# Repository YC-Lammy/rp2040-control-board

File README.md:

# rp2040-control-board
 a control board based on the rp2040

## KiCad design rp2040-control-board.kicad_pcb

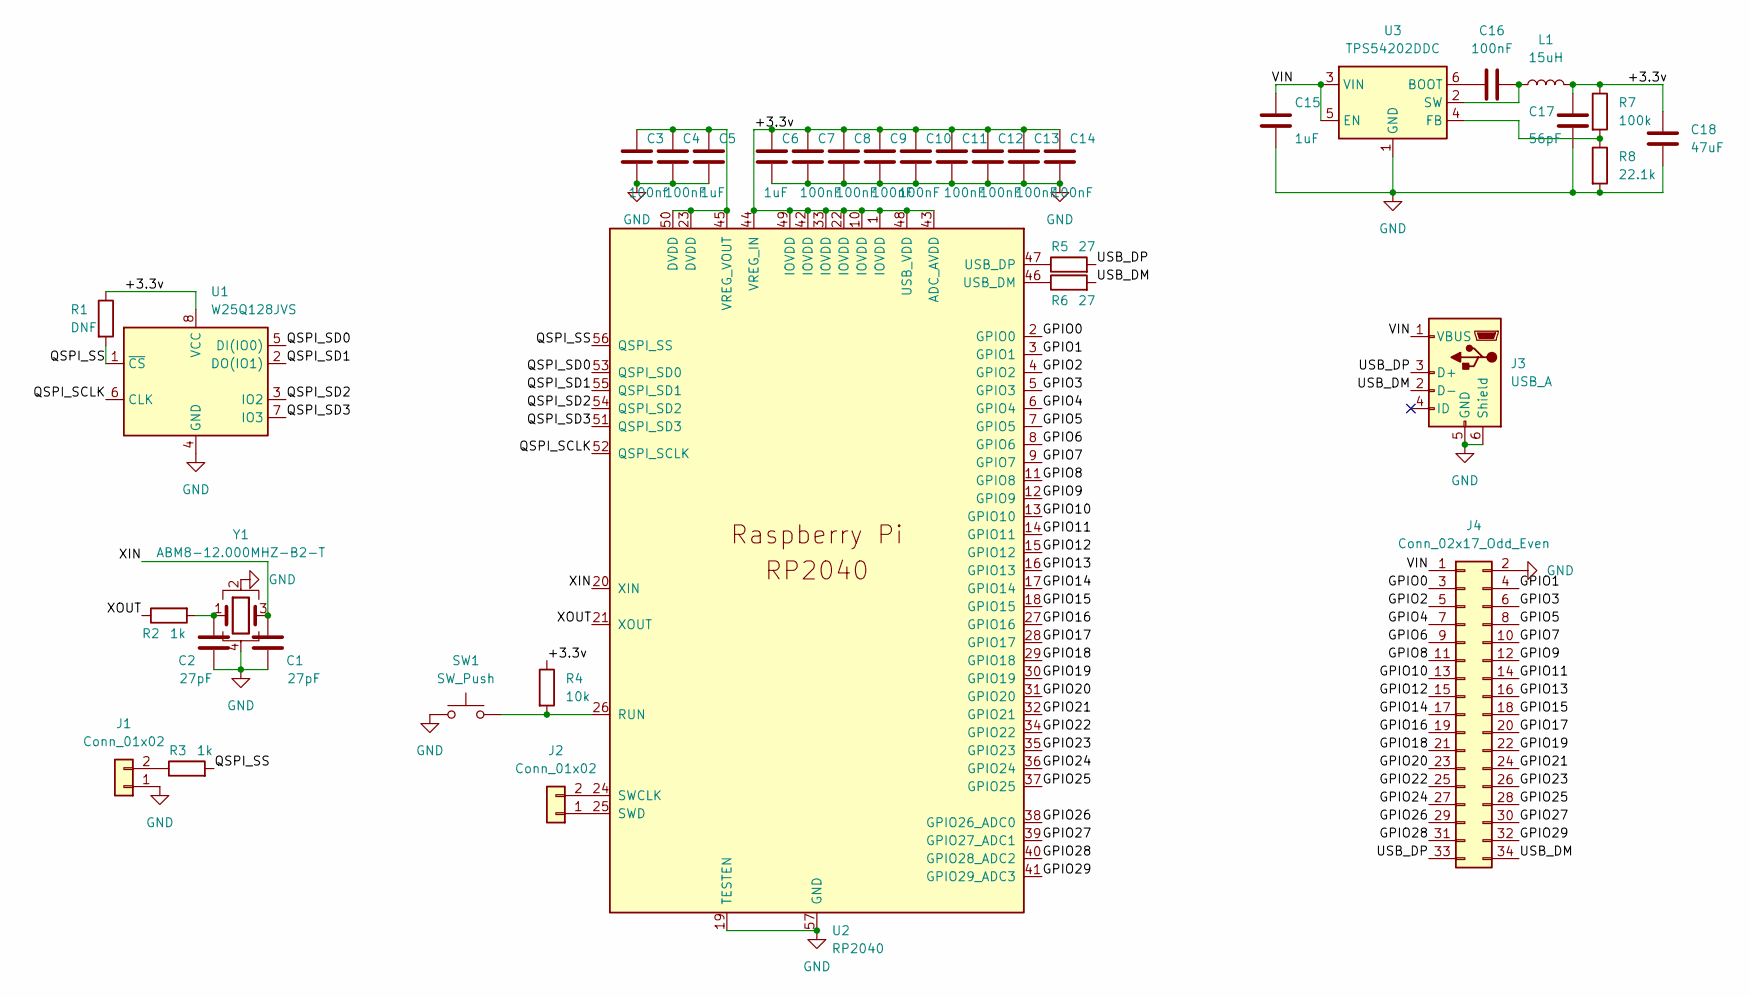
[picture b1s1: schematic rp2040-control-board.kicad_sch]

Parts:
C1, C2: 27pF; C_0603_1608Metric
C3: 100nf; C_0603_1608Metric
C4, C7, C8, C9, C10, C11, C12, C13, C14, C16: 100nF; C_0603_1608Metric
C5, C6, C15: 1uF; C_0603_1608Metric
C17: 56pF; C_0603_1608Metric
C18: 47uF; C_0603_1608Metric
J1, J2: Conn_01x02; PinHeader_1x02_P2.54mm_Vertical
J3: USB_A; USB_Micro-B_Amphenol_10103594-0001LF_Horizontal
J4: Conn_02x17_Odd_Even; PinHeader_2x17_P2.54mm_Horizontal
L1: 15uH; L_0805_2012Metric_Pad1.15x1.40mm_HandSolder
R1: DNF; R_0603_1608Metric
R2, R3: 1k; R_0603_1608Metric
R4: 10k; R_0603_1608Metric
R5, R6: 27; R_0603_1608Metric
R7: 100k; R_0603_1608Metric
R8: 22.1k; R_0603_1608Metric
SW1: SW_Push; SW_SPST_B3U-1000P
U1: W25Q128JVS; SOIC-8_5.23x5.23mm_P1.27mm
U2: RP2040; RP2040-QFN-56
U3: TPS54202DDC; SOT-23-6
Y1: ABM8-12.000MHZ-B2-T; Crystal_SMD_Abracon_ABM8G-4Pin_3.2x2.5mm

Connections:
/+3.3v: C6.1, C7.1, C8.1, C9.1, C10.1, C11.1, C12.1, C13.1, C14.1, C17.1, C18.1, L1.2, R1.1, R4.1, R7.1, U1.8 (VCC), U2.1 (IOVDD), U2.10 (IOVDD), U2.22 (IOVDD), U2.33 (IOVDD), U2.42 (IOVDD), U2.43 (ADC_AVDD), U2.44 (VREG_IN), U2.48 (USB_VDD), U2.49 (IOVDD)
/GPIO0: J4.3, U2.2 (GPIO0)
/GPIO1: J4.4, U2.3 (GPIO1)
/GPIO2: J4.5, U2.4 (GPIO2)
/GPIO3: J4.6, U2.5 (GPIO3)
/GPIO4: J4.7, U2.6 (GPIO4)
/GPIO5: J4.8, U2.7 (GPIO5)
/GPIO6: J4.9, U2.8 (GPIO6)
/GPIO7: J4.10, U2.9 (GPIO7)
/GPIO8: J4.11, U2.11 (GPIO8)
/GPIO9: J4.12, U2.12 (GPIO9)
/GPIO10: J4.13, U2.13 (GPIO10)
/GPIO11: J4.14, U2.14 (GPIO11)
/GPIO12: J4.15, U2.15 (GPIO12)
/GPIO13: J4.16, U2.16 (GPIO13)
/GPIO14: J4.17, U2.17 (GPIO14)
/GPIO15: J4.18, U2.18 (GPIO15)
/GPIO16: J4.19, U2.27 (GPIO16)
/GPIO17: J4.20, U2.28 (GPIO17)
/GPIO18: J4.21, U2.29 (GPIO18)
/GPIO19: J4.22, U2.30 (GPIO19)
/GPIO20: J4.23, U2.31 (GPIO20)
/GPIO21: J4.24, U2.32 (GPIO21)
/GPIO22: J4.25, U2.34 (GPIO22)
/GPIO23: J4.26, U2.35 (GPIO23)
/GPIO24: J4.27, U2.36 (GPIO24)
/GPIO25: J4.28, U2.37 (GPIO25)
/GPIO26: J4.29, U2.38 (GPIO26_ADC0)
/GPIO27: J4.30, U2.39 (GPIO27_ADC1)
/GPIO28: J4.31, U2.40 (GPIO28_ADC2)
/GPIO29: J4.32, U2.41 (GPIO29_ADC3)
/QSPI_SCLK: U1.6 (CLK), U2.52 (QSPI_SCLK)
/QSPI_SD0: U1.5 (DI(IO0)), U2.53 (QSPI_SD0)
/QSPI_SD1: U1.2 (DO(IO1)), U2.55 (QSPI_SD1)
/QSPI_SD2: U1.3 (IO2), U2.54 (QSPI_SD2)
/QSPI_SD3: U1.7 (IO3), U2.51 (QSPI_SD3)
/QSPI_SS: R1.2, R3.2, U1.1 (~CS), U2.56 (QSPI_SS)
/USB_DM: J3.2 (D-), J4.34, R6.2
/USB_DP: J3.3 (D+), J4.33, R5.2
/VIN: C15.1, J3.1 (VBUS), J4.1, U3.3 (VIN), U3.5 (EN)
/XIN: C1.2, U2.20 (XIN), Y1.3
/XOUT: R2.1, U2.21 (XOUT)
GND: C1.1, C2.1, C3.2, C4.2, C5.2, C6.2, C7.2, C8.2, C9.2, C10.2, C11.2, C12.2, C13.2, C14.2, C15.2, C17.2, C18.2, J1.1, J3.5 (GND), J3.6 (Shield), J4.2, R8.2, SW1.1, U1.4 (GND), U2.19 (TESTEN), U2.57 (GND), U3.1 (GND), Y1.2, Y1.4
unnamed: C2.2, R2.2, Y1.1
unnamed: C3.1, C4.1, C5.1, U2.23 (DVDD), U2.45 (VREG_VOUT), U2.50 (DVDD)
unnamed: C16.1, U3.6 (BOOT)
unnamed: C16.2, L1.1, U3.2 (SW)
unnamed: J1.2, R3.1
unnamed: J2.1, U2.25 (SWD)
unnamed: J2.2, U2.24 (SWCLK)
unnamed: R4.2, SW1.2, U2.26 (RUN)
unnamed: R5.1, U2.47 (USB_DP)
unnamed: R6.1, U2.46 (USB_DM)
unnamed: R7.2, R8.1, U3.4 (FB)

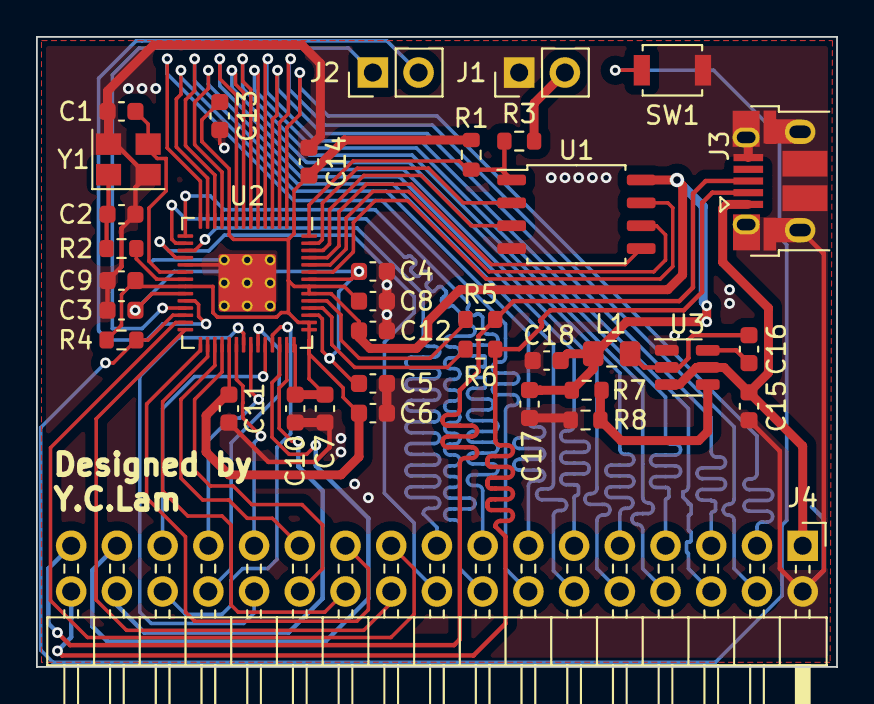
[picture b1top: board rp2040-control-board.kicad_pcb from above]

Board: 2 copper layers, 44.4 x 35.0 mm, 36 parts (0 on the bottom side), 54 nets.

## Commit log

2023-12-29 main
